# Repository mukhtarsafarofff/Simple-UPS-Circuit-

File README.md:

(DEU) Eine unterbrechungsfreie Stromversorgung (USV) ist für den Betrieb aller elektrischen Geräte erforderlich. Die Hauptaufgabe einer USV besteht darin, kurzfristig Notstrom zu liefern, wenn es zu einem vollständigen Ausfall oder Blackout der Stromversorgung kommt. Außerdem können die meisten modernen Online-USV-Anlagen eine Vielzahl von häufig auftretenden Stromproblemen korrigieren, einschließlich Spannungseinbrüchen: kurze Perioden, in denen die Spannung unter das normale Niveau der Stromversorgung fällt.  Um das Risiko von Datenverlusten, Ausfallzeiten und steigenden Kosten zu verringern, ist es wichtig, eine USV-Stromversorgung zu haben. Eine USV regelt kontinuierlich die eingehende Spannung und bietet bei einem Stromausfall eine Batterieunterstützung. Eine grundlegende USV-Schaltung wird die folgenden grundlegenden Stufen haben:

1) Wechselrichterschaltung
2) Eine Batterie
3) Eine Batterieladeschaltung
4) Eine Umschaltschaltung mit Relais oder anderen Geräten wie Triacs oder SSRs.
Der Wechselrichter: Da eine USV (Unterbrechungsfreie Stromversorgung) mit wichtigen und empfindlichen elektronischen Geräten umgehen muss, muss die involvierte Wechselrichterstufe in Bezug auf ihre Wellenform entsprechend fortschrittlich sein. Mit anderen Worten, ein gewöhnlicher Rechteckwellenwechselrichter ist für eine USV möglicherweise nicht geeignet.  Daher stellen wir bei unserem Design sicher, dass diese Bedingung angemessen berücksichtigt wird.

(ENG) An uninterruptible power supply are  required for the operation of all electrical devices. An uninterruptible power supply's primary role is to provide short-term emergency power when there's a complete mains failure or blackout. In addition, most modern online UPS can correct a wide range of common power problems, including: Sags: short periods when the voltage is below the usual mains supply level. To reduce the risk of data loss, downtime and increased costs, it is important to have a UPS power supply. A UPS continually regulates incoming voltage and provides battery backup in the event of a power failure. A basic UPS circuit will have the following fundamental stages:
1) Inverter circuit
2) A Battery
3) A battery charger circuit
4) A changeover circuit stage using relays or other devices such as triacs or SSRs

The Inverter: Since an UPS has to deal with crucial and sensitive electronic appliances, the involved inverter stage must be reasonably advanced with its waveform, in other words an ordinary square wave inverter may not be recommended for an UPS, and therefore for our design we make sure that this condition is aptly taken care of.

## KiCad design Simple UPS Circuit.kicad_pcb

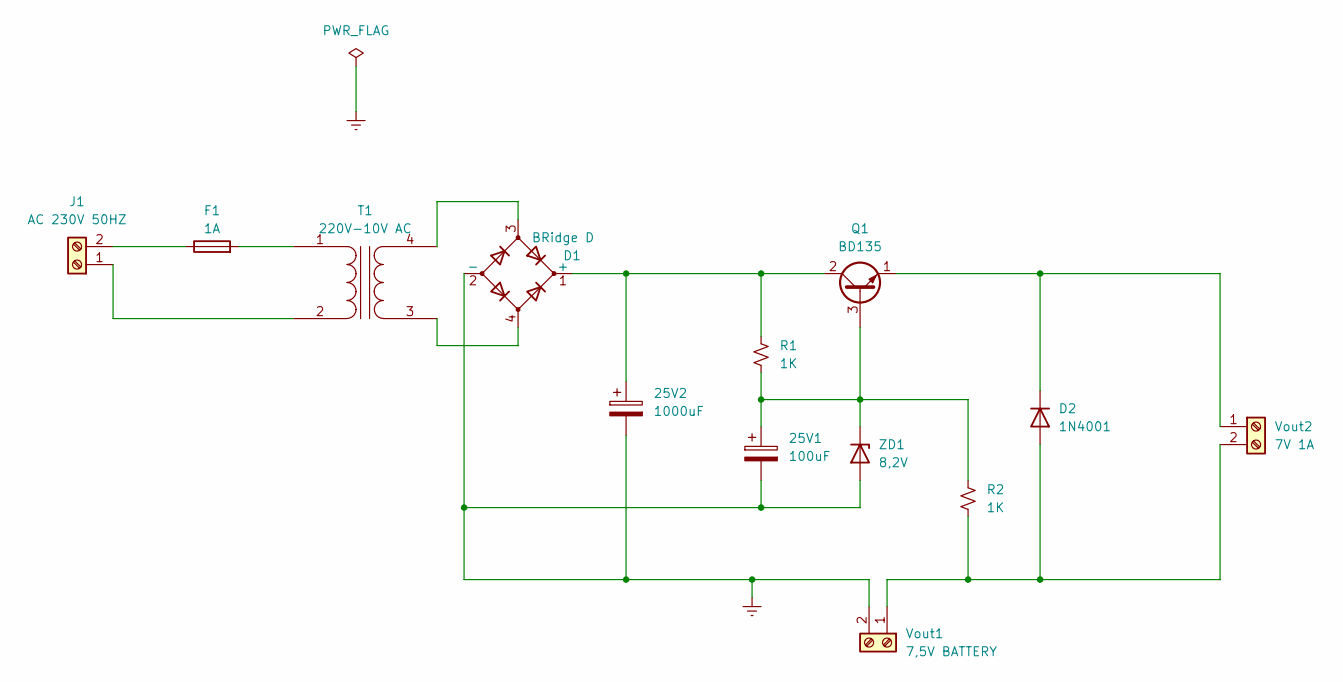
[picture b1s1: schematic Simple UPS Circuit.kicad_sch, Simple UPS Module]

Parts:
25V1: 100uF; CP_Radial_D10.0mm_P7.50mm
25V2: 1000uF; CP_Radial_D16.0mm_P7.50mm
D1: BRidge D; Diode_Bridge_IXYS_GUFP
D2: 1N4001; D_DO-41_SOD81_P10.16mm_Horizontal
F1: 1A; Fuse_Bourns_MF-RG900
J1: AC 230V 50HZ; TerminalBlock_bornier-2_P5.08mm
Q1: BD135; TO-126-3_Vertical
R1, R2: 1K; R_Axial_DIN0411_L9.9mm_D3.6mm_P15.24mm_Horizontal
T1: 220V-10V AC; Transformer_NF_ETAL_1-1_P1200
Vout1: 7,5V BATTERY; TerminalBlock_bornier-2_P5.08mm
Vout2: 7V 1A; TerminalBlock_bornier-2_P5.08mm
ZD1: 8,2V; D_DO-35_SOD27_P7.62mm_Horizontal

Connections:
Earth: 25V1.2, 25V2.2, D1.2 (-), Vout1.2, ZD1.2 (A)
unnamed: 25V2.1, D1.1 (+), Q1.2 (C), R1.2
unnamed: D2.2 (A), R2.1, Vout1.1, Vout2.2
unnamed: D2.1 (K), Q1.1 (E), Vout2.1
unnamed: J1.1, T1.2 (AB)
unnamed: F1.1, J1.2
unnamed: 25V1.1, Q1.3 (B), R1.1, R2.2, ZD1.1 (K)
unnamed: F1.2, T1.1 (AA)
unnamed: D1.4, T1.3 (SA)
unnamed: D1.3, T1.4 (SB)

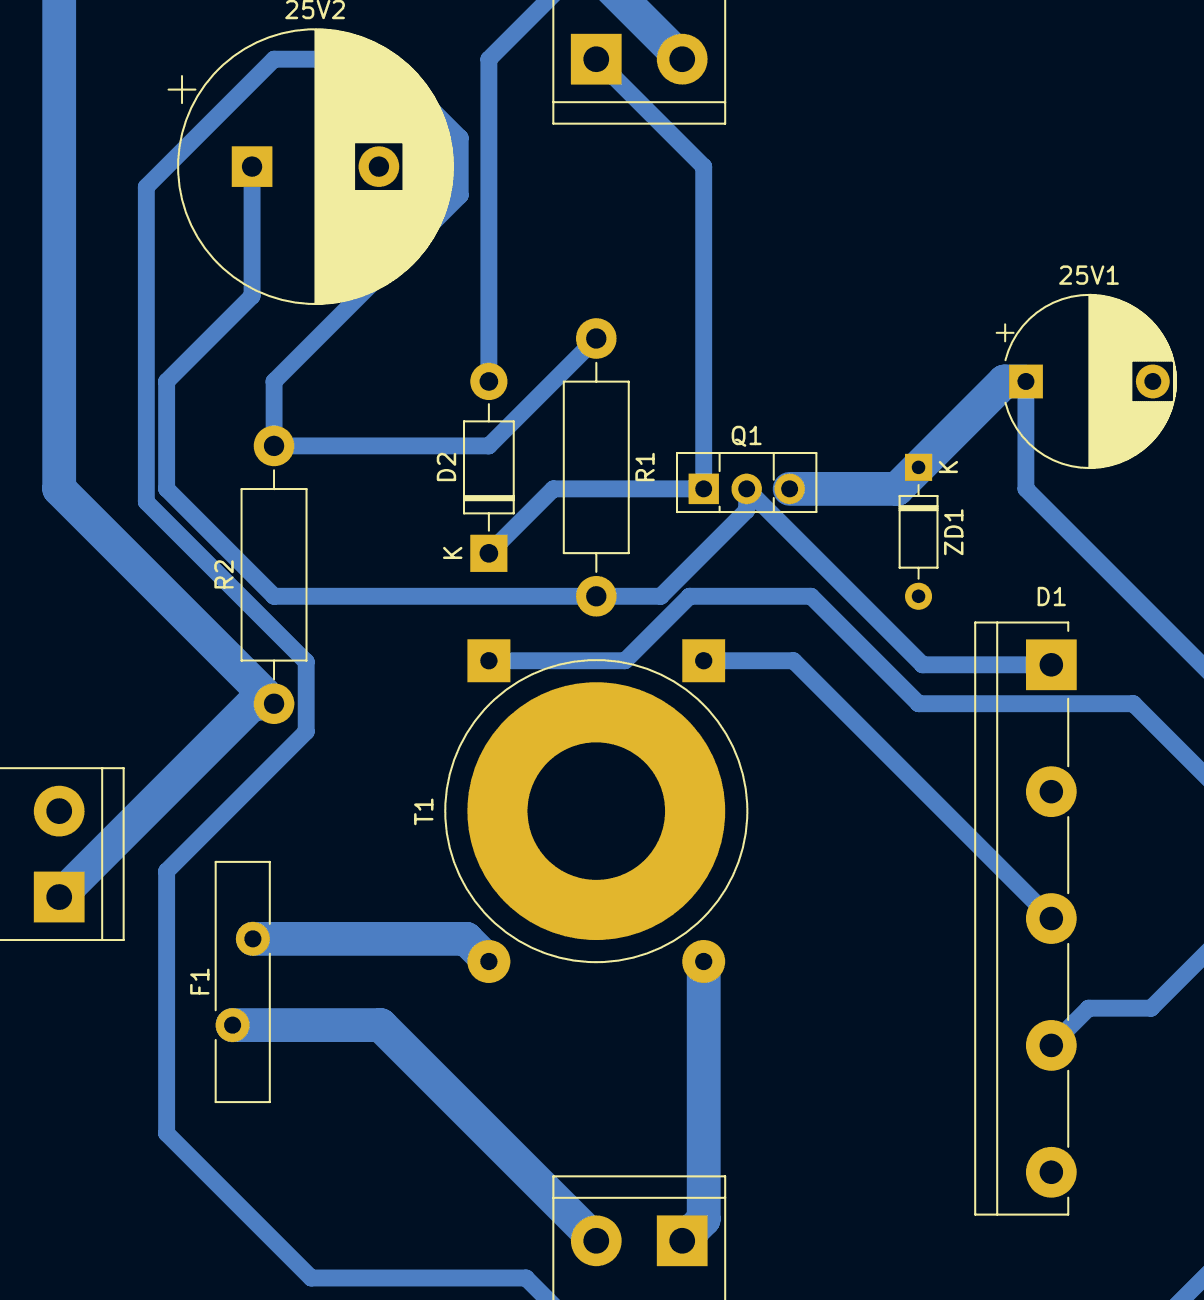
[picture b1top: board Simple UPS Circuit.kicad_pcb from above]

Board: 2 copper layers, 13 parts (0 on the bottom side), 10 nets.

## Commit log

2024-03-26 Simple UPS Circuit is accomplished
